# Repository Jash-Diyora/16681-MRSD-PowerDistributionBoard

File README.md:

# 16681: MRSD Project / Programming Familiarization - 1
## Jashkumar Diyora (jdiyora)
### README Questions

Note: Medium mode is set using startup.cpp

Q1. Write an overview of how your AI works, including how it detects where projectiles will fall and how it chooses where to go.  
Solution: A boolean vector `safeSpots` of size width+1 is constructed for each player at each time step, which is meant for recording which discretized position is safe and which is unsafe. I determine the values in it by considering the current explorations & projectiles. For explorations, as long as there is an exploration, I mark positions within the exploration range as unsafe. As for projectiles, after predicting when it will fall and where it would fall with basic physics knowledge, I mark the 2 positions at the left and the right of predicted falling point as unsafe if it will fall in the next 50 timesteps. This way, my AI would have enough time to escape from incoming missiles.

Q2. What challenges did you face when writing an AI?  
Solution: First part is understanding the physics behind it, some small cout statements could save big time as in to know that gravity is -9.81 and not 9.8, the center is 100, left is 0-100 and right is 100-200. Values greater than 200 and less than 0 were not much issue since it wont land on the spot we need to worry about. 

Q3. How well does your AI work on a Hard scenario? If it doesn’t work, why? If it does, try harder scenarios and see when it does fail and explain why?  
Solution: Lets talk about each levels:
1. Easy/Medium: Very similar behaviour in both levels since player speed variable is same with minor difference in enemy construct.
2. Hard: It was able to dodge it for a while but after a point it dies and may be major factor could be change explosion time with doubled launchers but still a bit satisfactory results.
3. Very hard/Impossible: I'd like to name this levels as instant death since defence barely worked out for 2 seconds.  
 
Q4. What did you think of the assignment and did it meet its goals? Why or why not?  
Solution: Although I had background in cpp but no doubt it is one of the most skill exhaustive coding assignment I have seen recently, I struggled a bit initially to acquire all the new cpp concepts since used in this project but it also gaved me a good idea of cpp file management system, and I even learnt about cmake and make.

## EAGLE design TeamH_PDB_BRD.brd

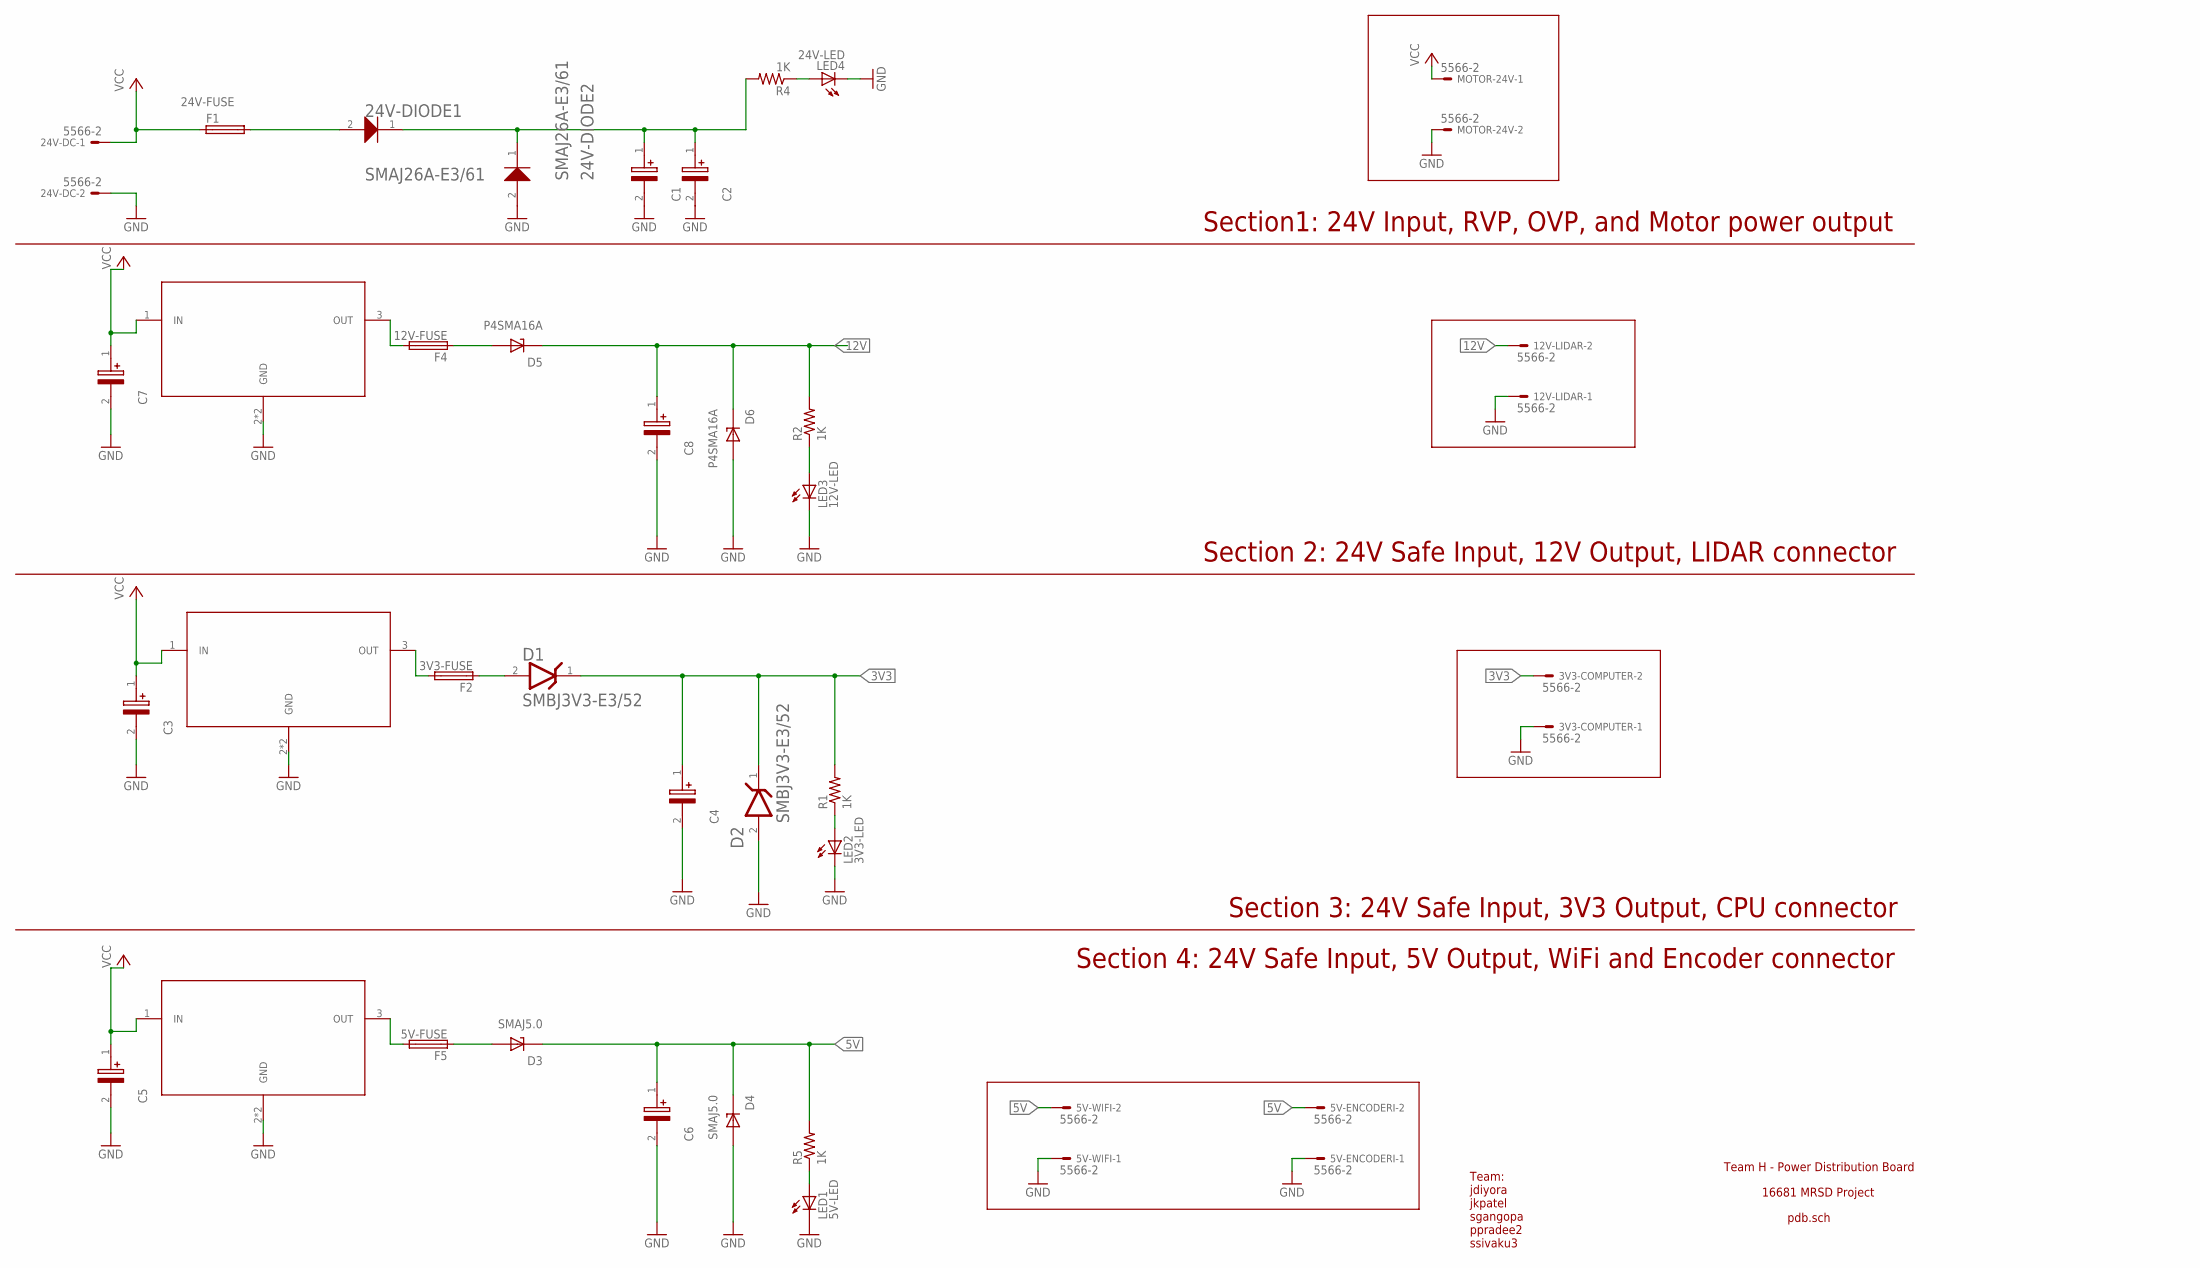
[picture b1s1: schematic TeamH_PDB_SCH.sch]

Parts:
3V3-COMPUTER, 5V-ENCODERI, 5V-WIFI, 12V-LIDAR, 24V-DC: 5566-2
24V-DIODE1, 24V-DIODE2: 24V TVS; VISHAY_SEMICONDUCTOR_SMAJ26A-E3-61_2
C1, C3, C4, C5, C6, C7, C8: 0.1uF; CAPPM3216X180N
C2: 10uF; CAPPM3216X180N
D1, D2: VISHAY_SMBJ3V3-E3-52VISHAY_SMBJ3V3-E3-52_0_0; VISHAY_SMBJ3V3-E3-52_0
D3, D4: SMAJ5.0; DIOM4325X250N
D5, D6: P4SMA16A; DIOM4325X250N
F1: 24V-FUSE; TE5
F2: 3V3-FUSE; TE5
F4: 12V-FUSE; TE5
F5: 5V-FUSE; TE5
LED1: 5V-LED; CHIPLED_1206
LED2: 3V3-LED; CHIPLED_1206
LED3: 12V-LED; CHIPLED_1206
LED4: 24V-LED; CHIPLED_1206
MIC29300-3V3: 3v3; TO263
MIC29300-5V: 5v; TO263
MIC29300-12V: 12v; TO263
MOTOR-24V: 5566-2
R1, R2, R4, R5: 1K; R1206

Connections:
3V3: 3V3-COMPUTER.2, C4.1 (+), D1.1 (CATHODE), D2.1 (CATHODE), R1.2
5V: 5V-ENCODERI.2, 5V-WIFI.2, C6.1 (+), D3.C, D4.C, R5.2
12V: 12V-LIDAR.2, C8.1 (+), D5.C, D6.C, R2.2
24VSAFE: 24V-DIODE1.1 (K), 24V-DIODE2.1 (K), C1.1 (+), C2.1 (+), R4.2
GND: 3V3-COMPUTER.1, 5V-ENCODERI.1, 5V-WIFI.1, 12V-LIDAR.1, 24V-DC.2, 24V-DIODE2.2 (A), C1.2 (-), C2.2 (-), C3.2 (-), C4.2 (-), C5.2 (-), C6.2 (-), C7.2 (-), C8.2 (-), D2.2 (ANODE), D4.A, D6.A, LED1.C, LED2.C, LED3.C, LED4.C, MIC29300-3V3.2 (GND), MIC29300-3V3.GND@ (GND), MIC29300-5V.2 (GND), MIC29300-5V.GND@ (GND), MIC29300-12V.2 (GND), MIC29300-12V.GND@ (GND), MOTOR-24V.2
unnamed: 24V-DIODE1.2 (A), F1.2
unnamed: F5.2, MIC29300-5V.3 (OUT)
unnamed: F4.2, MIC29300-12V.3 (OUT)
unnamed: D3.A, F5.1
unnamed: D5.A, F4.1
unnamed: LED4.A, R4.1
unnamed: F2.2, MIC29300-3V3.3 (OUT)
unnamed: D1.2 (ANODE), F2.1
unnamed: LED1.A, R5.1
unnamed: LED3.A, R2.1
unnamed: LED2.A, R1.1
VCC: 24V-DC.1, C3.1 (+), C5.1 (+), C7.1 (+), F1.1, MIC29300-3V3.1 (IN), MIC29300-5V.1 (IN), MIC29300-12V.1 (IN), MOTOR-24V.1

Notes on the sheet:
Team H - Power Distribution Board
16681 MRSD Project
pdb.sch
Team: jdiyora jkpatel sgangopa ppradee2 ssivaku3
Section1: 24V Input, RVP, OVP, and Motor power output
Section 2: 24V Safe Input, 12V Output, LIDAR connector
Section 3: 24V Safe Input, 3V3 Output, CPU connector
Section 4: 24V Safe Input, 5V Output, WiFi and Encoder connector

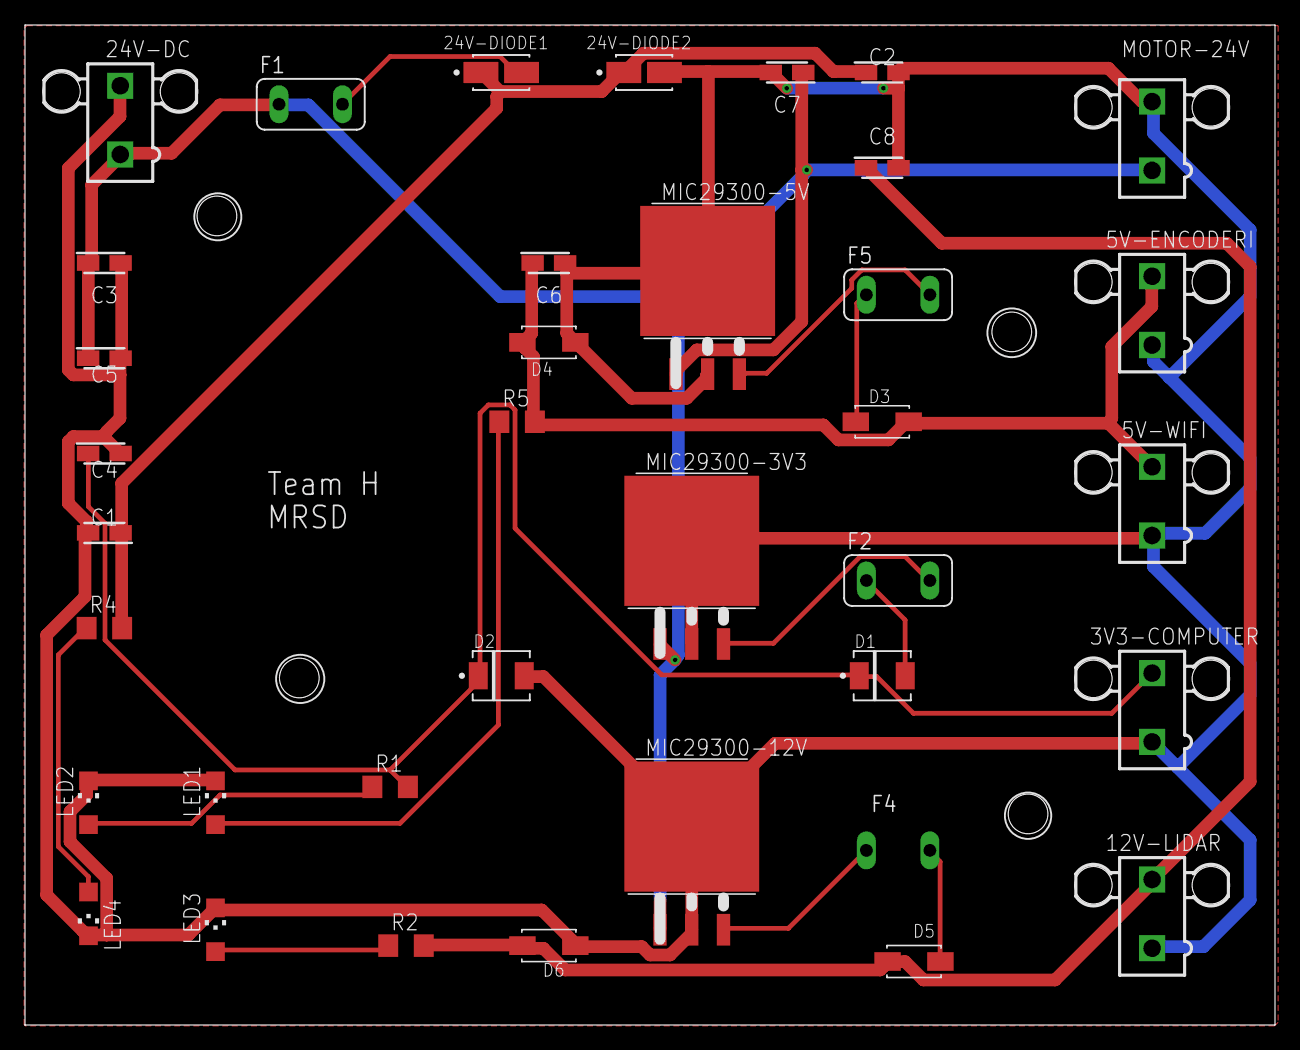
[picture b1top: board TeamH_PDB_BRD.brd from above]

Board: 2 copper layers, 100.0 x 80.0 mm, 37 parts (1 on the bottom side), 17 nets.
